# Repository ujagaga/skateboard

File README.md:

# DIY Electric Skateboard With Hoverboard Wheels

This is the 3D model for my DIY electric skateboard. It features two howerboard motor whells and 2 passive wheels. 
The driver is from AliExpress, "36V Brushless Dual Motor Electric Skateboard Controller with remote controller":

https://www.aliexpress.com/item/1005004489103885.html?spm=a2g0o.order_list.order_list_main.116.c24d18024PqocZ

The heatsink on the original driver is small and the first electronics I used burned up, so I installed a larger heatsink.

The battery I am using is from a hoverboard as those are the cheapest ones available to me. 
To get more range, I connected two batteries in paralell.

The charge port is for Xiaomi electric scooter, so I am re-using the charger I already have.

The front light is a white LED strip 10mm wide. There is a transparent plastic window covering the LED strip.
The rear light is made using a red COB LED strip with a silicone covering the LEDs, so no need for an additional plastic to protect it. 

# How to
- The screws I used are standard self curving screws for wood 3x30mm and 3x25mm.

# NOTE
I did build one using my own code for ESP8266 WiFi modules. There was a remote controller and controll circuit for a motor driver
I bought online. The whole thing worked well, but used a 90mm hub motor wheel. The bicycle tracks in my town are not that great, 
so I decided to build a new one with two howerboard wheels. The whole electronics is so cheap that it really makes no sence to develop it myself,
which is why I dropped the development and just used the factory made stuff.

Downside:
1. The LED light port is very small and I could not find a connector for it and no documentation or a module to buy to connect. 
Will use the battery indicator wires to trigger the lights.
3. The HALL sensors are not very well tuned so I disconnected them entirely. It works well without them. 

# Contact
ujagaga@gmail.com

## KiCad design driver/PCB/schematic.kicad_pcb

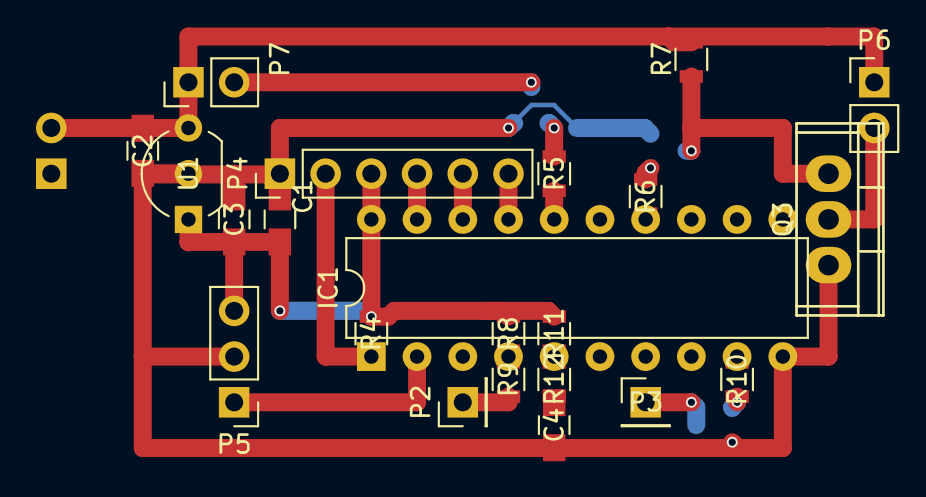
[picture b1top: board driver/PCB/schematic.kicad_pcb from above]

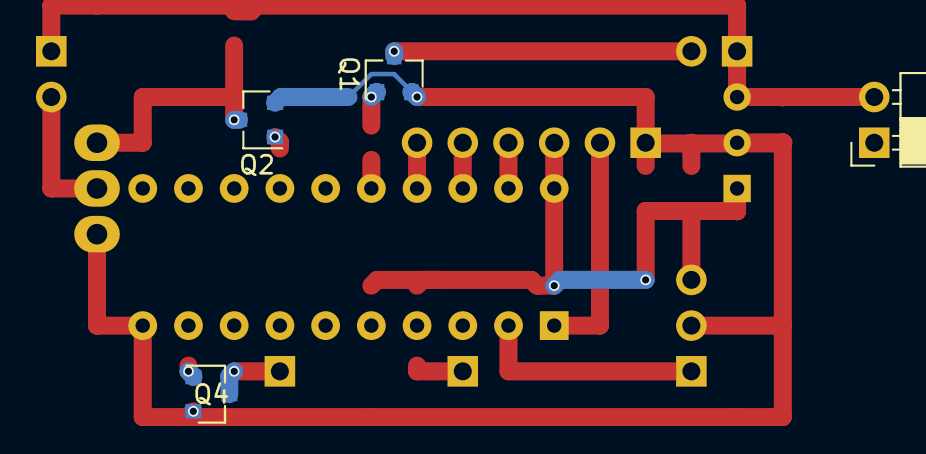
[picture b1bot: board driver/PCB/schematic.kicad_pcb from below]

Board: 2 copper layers, 26 parts (4 on the bottom side), 22 nets.

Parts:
C1: 100n; C_0805_HandSoldering
C2, C3: 4u7; C_0805_HandSoldering
C4: 10n; C_0805_HandSoldering
IC1: ATTINY2313-P; DIP-20_W7.62mm
P2: Capacitive sensor; Socket_Strip_Straight_1x01_Pitch2.54mm
P3: Siren; Socket_Strip_Straight_1x01_Pitch2.54mm
P4: Programming; Socket_Strip_Straight_1x06_Pitch2.54mm
P5: Rx; Socket_Strip_Straight_1x03_Pitch2.54mm
P6: PWM_OUT; Socket_Strip_Straight_1x02_Pitch2.54mm
P7: LED_PWR; Socket_Strip_Straight_1x02_Pitch2.54mm
Q1, Q2, Q4: BC817-40; SOT-23
Q3: IRF640N; TO-220
R4, R6, R7: 10K; R_0805
R5, R9, R10, R12: 1K; R_0805
R8, R11: 1M; R_0805
SW1: SPST; Socket_Strip_Angled_1x02_Pitch2.54mm
U1: LM78L05ACZ; TO-92_Inline_Wide

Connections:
GNDREF: C1.1, C2.2, C3.2, C4.1, IC1.10, P4.1, P5.2, Q1.2, Q2.2, Q3.3, Q4.2, U1.2
unnamed: C1.2, C3.1, IC1.20, P4.3, P5.3, R4.1, R8.2, R11.2, U1.1
unnamed: C2.1, P6.1, P7.1, R7.2, SW1.2, U1.3
unnamed: C4.2, R12.1
unnamed: IC1.1, P4.2, R4.2
unnamed: IC1.2, P5.1
unnamed: IC1.4, R8.1, R9.1
unnamed: IC1.5, R11.1, R12.2
unnamed: IC1.9, R10.2
unnamed: IC1.14, R6.2
unnamed: IC1.16, R5.2
unnamed: IC1.17, P4.6
unnamed: IC1.18, P4.5
unnamed: IC1.19, P4.4
unnamed: P2.1, R9.2
unnamed: P3.1, Q4.3
unnamed: P6.2, Q3.2
unnamed: P7.2, Q1.3
unnamed: Q1.1, R5.1
unnamed: Q2.1, R6.1
unnamed: Q2.3, Q3.1, R7.1
unnamed: Q4.1, R10.1

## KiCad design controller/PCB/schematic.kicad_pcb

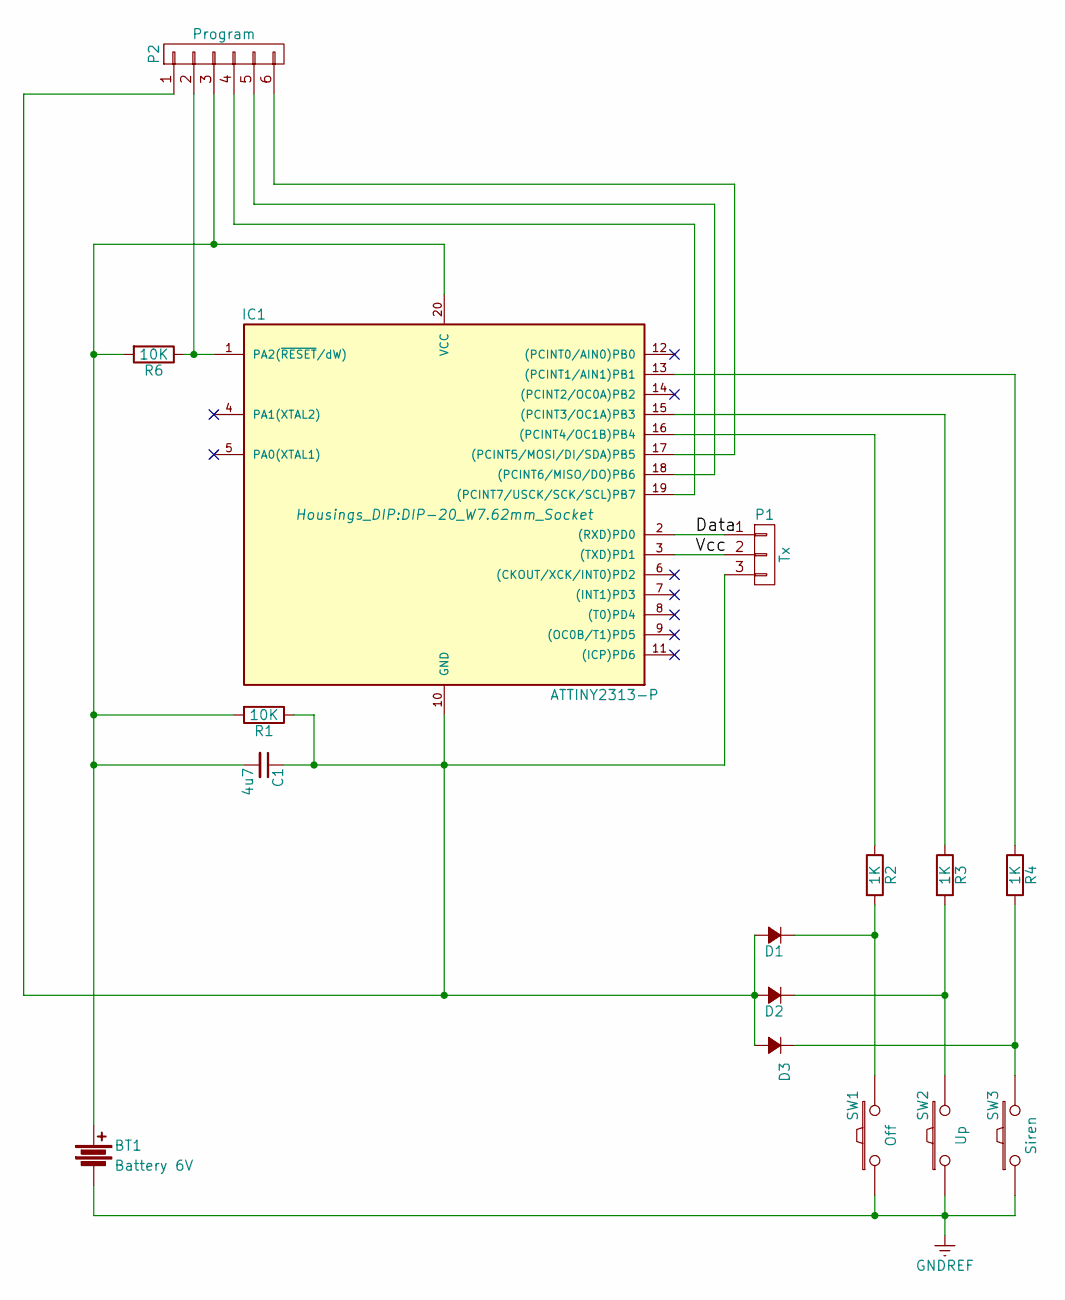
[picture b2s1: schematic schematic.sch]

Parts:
BT1: Battery 6V; 6V_battery_4LR44
C1: 4u7; C_0805_HandSoldering
D1, D2, D3: D; D_0805
IC1: ATTINY2313-P; DIP-20_W7.62mm_Socket
P1: Tx; Socket_Strip_Straight_1x03_Pitch2.54mm
P2: Program; Socket_Strip_Straight_1x06_Pitch2.54mm
R1, R6: 10K; R_0805_HandSoldering
R2, R3, R4: 1K; R_0805_HandSoldering
SW1: Off; Socket_Strip_Straight_1x02_Pitch2.54mm
SW2: Up; Socket_Strip_Straight_1x02_Pitch2.54mm
SW3: Siren; Socket_Strip_Straight_1x02_Pitch2.54mm

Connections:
GNDREF: BT1.2, SW1.1, SW2.1, SW3.1
unnamed: BT1.1, C1.2, IC1.20 (VCC), P2.3, R1.2, R6.2
unnamed: C1.1, D1.2 (A), D2.2 (A), D3.2 (A), IC1.10 (GND), P1.3, P2.1, R1.1
unnamed: D1.1 (K), R2.2, SW1.2
unnamed: D2.1 (K), R3.2, SW2.2
unnamed: D3.1 (K), R4.2, SW3.2
unnamed: IC1.1 (PA2(~RESET~/dW)), P2.2, R6.1
unnamed: IC1.2 ((RXD)PD0), P1.1
unnamed: IC1.3 ((TXD)PD1), P1.2
unnamed: IC1.13 ((PCINT1/AIN1)PB1), R4.1
unnamed: IC1.15 ((PCINT3/OC1A)PB3), R3.1
unnamed: IC1.16 ((PCINT4/OC1B)PB4), R2.1
unnamed: IC1.17 ((PCINT5/MOSI/DI/SDA)PB5), P2.6
unnamed: IC1.18 ((PCINT6/MISO/DO)PB6), P2.5
unnamed: IC1.19 ((PCINT7/USCK/SCK/SCL)PB7), P2.4

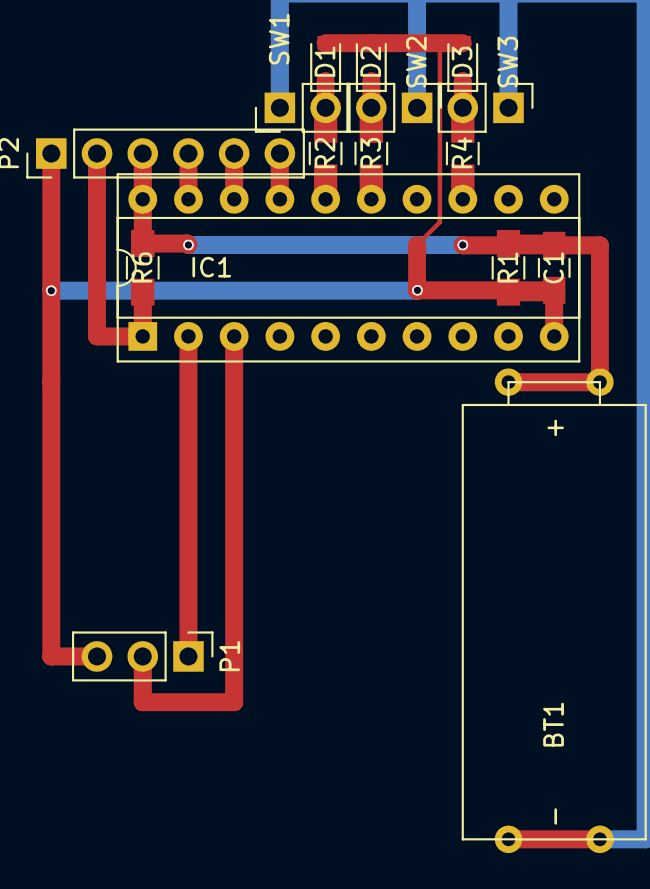
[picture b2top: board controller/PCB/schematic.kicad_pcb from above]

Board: 2 copper layers, 16 parts (0 on the bottom side), 15 nets.

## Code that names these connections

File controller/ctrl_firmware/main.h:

/*
 * main.h
 *
 *  Created on: Oct 24, 2016
 *      Author: rada
 */

#ifndef MAIN_H_
#define MAIN_H_

/* Configuration */
#define TX_PWR_PIN		(PD0)
#define TX_DATA_PIN		(PD1)

#define SW_SIREN_PIN	(PB1)
#define SW_UP_PIN		(PB3)
#define SW_OFF_PIN		(PB4)
/* End of configuration */

#define TX_PWR_MASK		(1 << TX_PWR_PIN)
#define TX_DATA_MASK	(1 << TX_DATA_PIN)
#define SW_SIREN_MASK	(1 << SW_SIREN_PIN)
#define SW_UP_MASK		(1 << SW_UP_PIN)
#define SW_OFF_MASK		(1 << SW_OFF_PIN)

#endif /* MAIN_H_ */

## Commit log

2017-05-12 * controller schematic and pcb * driver schematic and pcb * controller firmware * driver firmware
2017-05-12 Added read.me
2017-05-13 Updated firmware and schematic
2017-05-13 Switched to new command system
2017-05-14 Finished first functional version of driver
2019-01-09 Updated docs for new koncept
2019-01-10 Added Arduino sketches from the IOT project
2019-01-10 Simplified and removed HTTP and WEBSOCKETS
2019-01-11 Added schematic
2019-01-11 Added BLDC Motor CTRL logic
2019-01-25 Updated Sketch
2019-01-26 Added commands
2019-01-30 Added remote
2019-01-30 Added remote ctrl schematic
2019-01-30 Added battery charging
2019-01-31 Minor tweeks
2019-07-28 Adjusted for new board
2019-07-28 Fixed break
2019-09-29 Add bopxes 3d print models
2019-09-30 Remote ctrl box improovements
2019-09-30 Updated remote ctrl box
2019-10-01 Remote ctrl box work
2019-10-01 Finished remote box
2019-10-03 RemorteCTRL box finished
2019-10-04 New remote ctrl schematic
2019-10-07 Design proposition
2019-10-14 new box model
2019-10-15 Updated boxes
2019-10-15 Added protector
2019-10-15 Finished Protector
2019-10-15 Updated boxes to follow board radius
2019-10-16 Updated protectot
2019-10-17 Updated protector height
2019-10-25 Updated skate remote
2019-10-26 Finished remote controller
2019-10-27 Updated skate receiver
2019-10-31 Improoved receiver
2019-10-31 Updated remote controller for faster server disconnect detection
2019-11-01 Add server beacon
2019-11-01 Minor fix
2019-11-01 Honk added
2019-11-01 Finished the remote controller
2019-11-01 Add honk support
2019-11-01 Finishe honk support
2020-01-26 Working fw
2020-01-27 Updated REMOTE CONTROLLER BOX
2021-05-23 Fixed honk
2021-08-20 New schenatic and 3d models
2021-08-21 New version
2022-05-15 Updated the new box
2022-05-16 New box
2024-03-30 Add battery box holder
2024-04-02 Add battery box
2024-04-02 Remote ctrl box fix
2024-04-04 Working version
2024-04-07 Fixed receiver driver
2024-04-07 Fixed version
2024-04-07 Reduced remote ctrl timeout
2024-04-07 sw Upgrade
2024-04-07 New lamp
2024-04-08 Corrected RemoteCtrl box
2024-07-13 Add HowerboardWheelAdapter
2024-07-13 Factory made electronics
2024-07-23 Add howerboard wheel adapter and mudguard
2024-07-23 Removed ESP8266 setup
2024-07-24 BoxSize adjustment
2024-07-25 Fixed wheel adapter
2024-07-30 Updated lights
2024-08-04 Optimized pwrBox
2024-08-04 Test
2024-08-06 Lamp update
2024-08-06 Lamp improovement
2024-08-13 Add rear wheel adapter
2025-04-18 DIY controller
2025-04-18 New version with factory made controller
2025-04-18 New Handle
2025-05-04 V2 start
2025-05-11 Finished PwrBox
2025-05-17 Electronic box
2025-05-18 Removed obsolete pwr box
2025-07-12 Add whellAdapter
2025-07-15 Add wheel adapter
2025-07-15 Renamed wheel adapters
2025-08-06 New headlight
2025-08-09 Latest
2025-08-10 Finished lights
2025-08-10 Add Ender3 STL and GCode
2025-08-10 Updated screw sizes
2025-08-10 Updated model names
2025-08-10 Correction
2025-08-23 Update power box
2025-08-30 PwrBox update
2025-09-05 New boxes
2025-09-07 Updated distancer
2025-09-07 NEw wheel adpter
2025-09-08 Started new clip
2025-09-08 Updated the hook
2025-09-11 V3 rear lamp top
